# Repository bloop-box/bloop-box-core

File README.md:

# bloop-box-core

[Hardware Documentation](https://bloop-box.github.io/bloop-box-core)

### !!! THIS IS A PROTOTYPE WORK IN PROGRESS !!!

## What does it do?

This board is supposed to replace the Raspberry Pi Zero 2W in the bloop box with a cheaper alternative, using an ESP32-C5.

It will support all functions of the bloop box and can be used as a drop-in-replacement for the Raspi. In addition, due to the capabilities of the ESP32-C5 this will have support for 5GHz WiFi.

## GPIO

| Function       | ESP-Pin |
|:---------------|:--------|
| Button1 (BOOT) | GPIO 28 |
| Button2        | GPIO 27 |
| LED1           | GPIO 25 |
| LED2           | GPIO 26 |
| I2C SCL        | GPIO 3  |
| I2C SDA        | GPIO 2  |
| I2S BCLK       | GPIO 23 |
| I2S DIN        | GPIO 4  |
| I2S LRCLK      | GPIO 24 |
| SPI MISO       | GPIO 9  |
| SPI MOSI       | GPIO 8  |
| SPI SCK        | GPIO 6  |
| NFC CS         | GPIO 10 |
| NFC IRQ        | GPIO 0  |
| NFC RST        | GPIO 1  |
| SD CS          | GPIO 5  |
| SD Detect      | GPIO 7  |
| Serial RX      | GPIO 12 |
| Serial TX      | GPIO 11 |

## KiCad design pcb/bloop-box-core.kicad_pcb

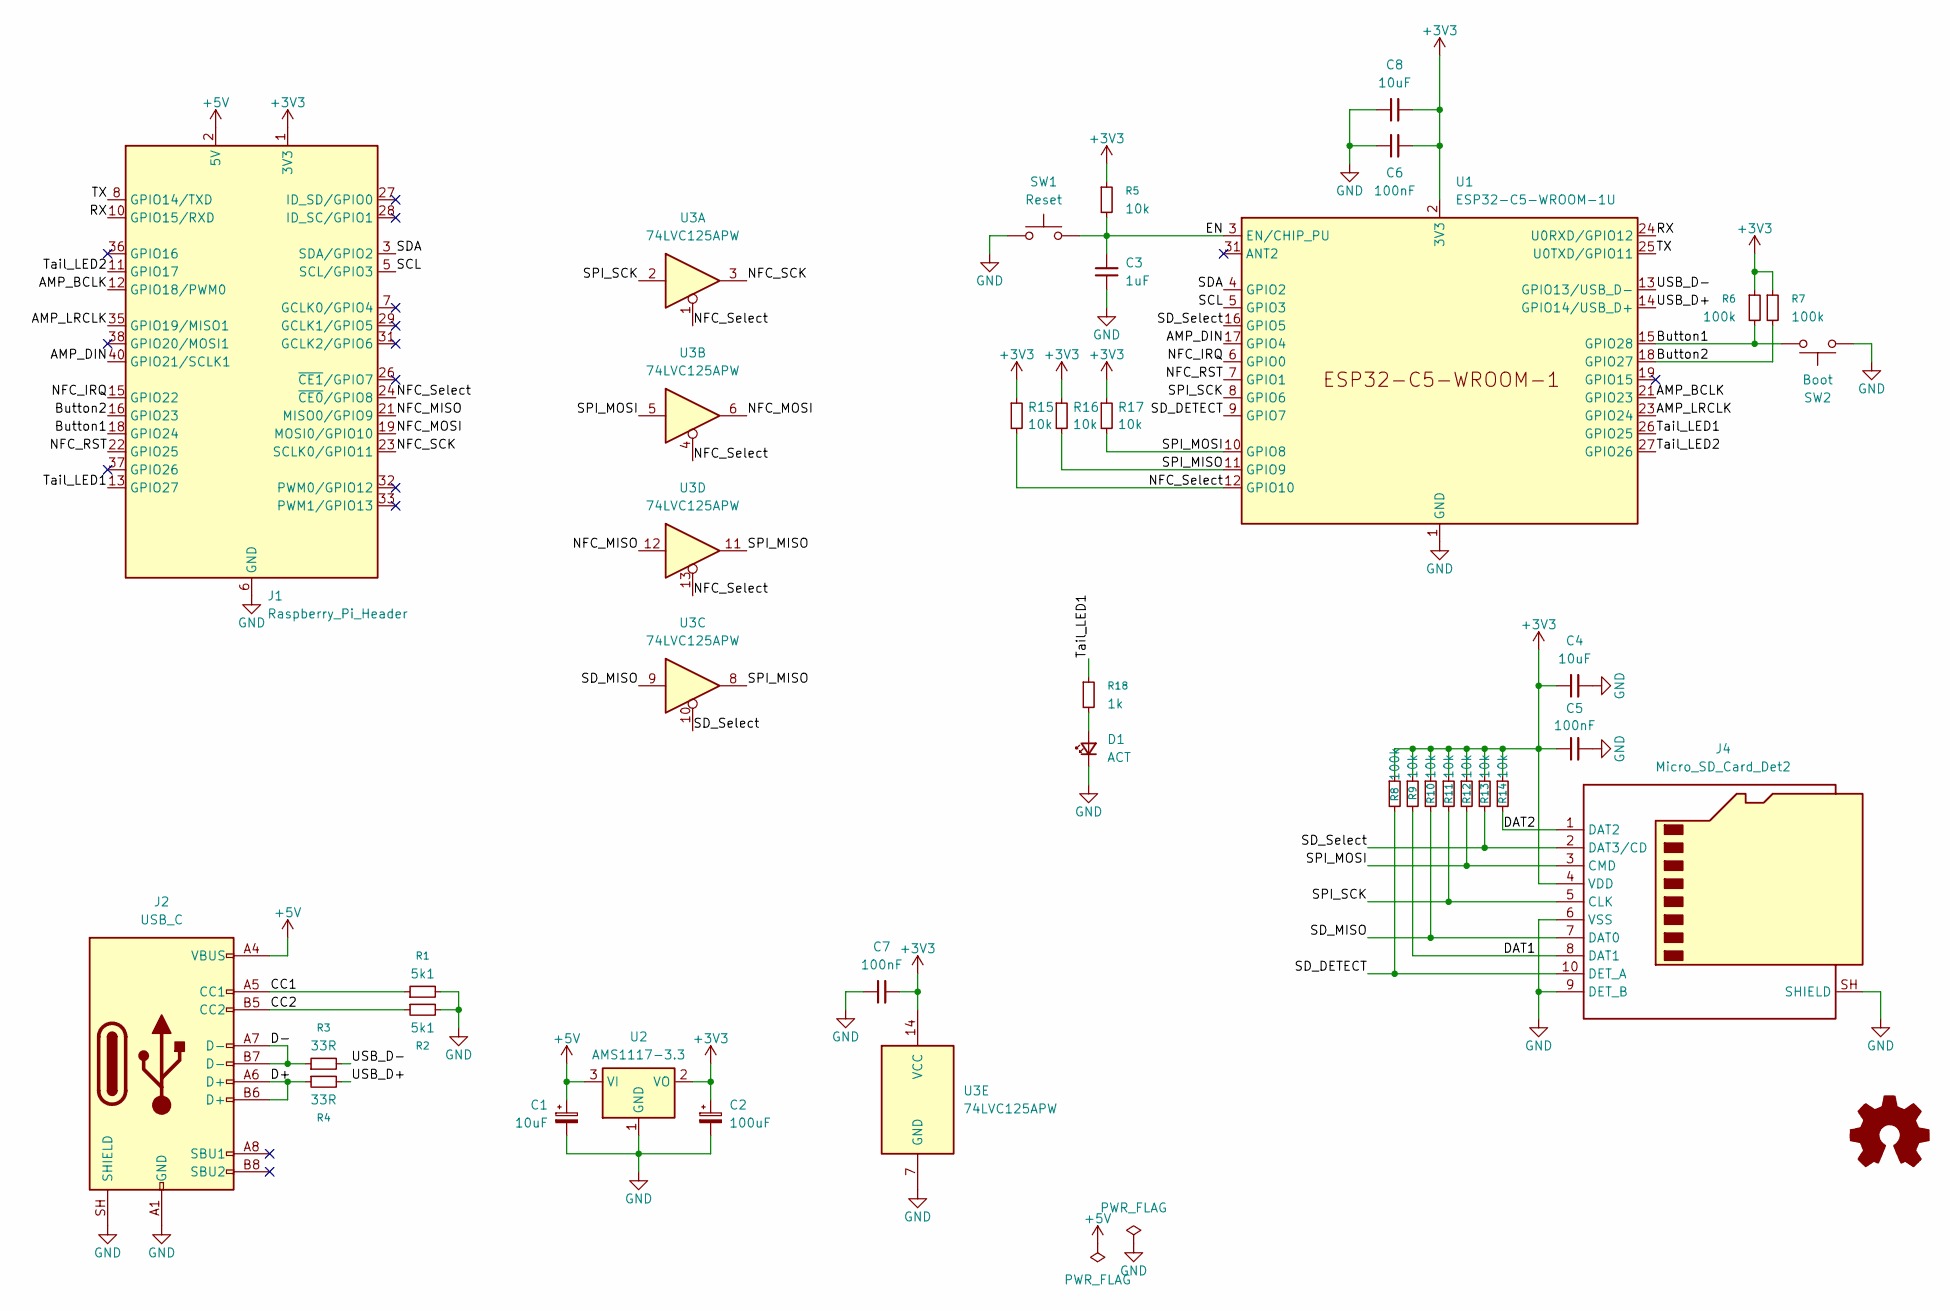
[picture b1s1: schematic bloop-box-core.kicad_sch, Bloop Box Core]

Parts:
C1: 10uF; CP_EIA-3216-18_Kemet-A; LCSC C7171
C2: 100uF; CP_EIA-3528-21_Kemet-B; LCSC C16133
C3: 1uF; C_0402_1005Metric; LCSC C52923
C4, C8: 10uF; C_0402_1005Metric; LCSC C15525
C5, C6, C7: 100nF; C_0402_1005Metric; LCSC C1525
D1: ACT; LED_0603_1608Metric; LCSC C89811
J1: Raspberry_Pi_Header; PinHeader_2x20_P2.54mm_Vertical; LCSC C50980
J2: USB_C; USB_C_Receptacle_GCT_USB4105-xx-A_16P_TopMnt_Horizontal; LCSC C2765186
J4: Micro_SD_Card_Det2; microSD_HC_Molex_104031-0811; LCSC C585350
R1, R2: 5k1; R_0402_1005Metric; LCSC C25905
R3, R4: 33R; R_0402_1005Metric; LCSC C25105
R5, R9, R10, R11, R12, R13, R14, R15, R16, R17: 10k; R_0402_1005Metric; LCSC C25744
R6, R7, R8: 100k; R_0402_1005Metric; LCSC C25741
R18: 1k; R_0402_1005Metric; LCSC C11702
SW1: Reset; SW_Push_SPST_NO_Alps_SKRK; LCSC C720477
SW2: Boot; SW_Push_SPST_NO_Alps_SKRK; LCSC C720477
U1: ESP32-C5-WROOM-1U; LCSC C54951857
U2: AMS1117-3.3; SOT-223-3_TabPin2; LCSC C6186
U3: 74LVC125APW; TSSOP-14_4.4x5mm_P0.65mm; LCSC C6059

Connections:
+3V3: C2.1, C4.2, C5.2, C6.2, C7.2, C8.1, J1.1 (3V3), J1.17 (3V3), J4.4 (VDD), R5.1, R6.1, R7.1, R8.1, R9.1, R10.1, R11.1, R12.1, R13.1, R14.1, R15.1, R16.1, R17.1, U1.2 (3V3), U2.2 (VO), U3.14 (VCC)
+5V: C1.1, J1.2 (5V), J1.4 (5V), J2.A4 (VBUS), J2.A9 (VBUS), J2.B4 (VBUS), J2.B9 (VBUS), U2.3 (VI)
/AMP_BCLK: J1.12 (GPIO18/PWM0), U1.21 (GPIO23)
/AMP_DIN: J1.40 (GPIO21/SCLK1), U1.17 (GPIO4)
/AMP_LRCLK: J1.35 (GPIO19/MISO1), U1.23 (GPIO24)
/Button1: J1.18 (GPIO24), R6.2, SW2.1, U1.15 (GPIO28)
/Button2: J1.16 (GPIO23), R7.2, U1.18 (GPIO27)
/CC1: J2.A5 (CC1), R1.1
/CC2: J2.B5 (CC2), R2.1
/D+: J2.A6 (D+), J2.B6 (D+), R4.1
/D-: J2.A7 (D-), J2.B7 (D-), R3.1
/DAT1: J4.8 (DAT1), R9.2
/DAT2: J4.1 (DAT2), R14.2
/EN: C3.1, R5.2, SW1.2, U1.3 (EN/CHIP_PU)
/NFC_IRQ: J1.15 (GPIO22), U1.6 (GPIO0)
/NFC_MISO: J1.21 (MISO0/GPIO9), U3.12
/NFC_MOSI: J1.19 (MOSI0/GPIO10), U3.6
/NFC_RST: J1.22 (GPIO25), U1.7 (GPIO1)
/NFC_SCK: J1.23 (SCLK0/GPIO11), U3.3
/NFC_Select: J1.24 (~CE0/GPIO8), R15.2, U1.12 (GPIO10), U3.1, U3.4, U3.13
/RX: J1.10 (GPIO15/RXD), U1.24 (U0RXD/GPIO12)
/SCL: J1.5 (SCL/GPIO3), U1.5 (GPIO3)
/SDA: J1.3 (SDA/GPIO2), U1.4 (GPIO2)
/SD_DETECT: J4.10 (DET_A), R8.2, U1.9 (GPIO7)
/SD_MISO: J4.7 (DAT0), R10.2, U3.9
/SD_Select: J4.2 (DAT3/CD), R13.2, U1.16 (GPIO5), U3.10
/SPI_MISO: R16.2, U1.11 (GPIO9), U3.8, U3.11
/SPI_MOSI: J4.3 (CMD), R12.2, R17.2, U1.10 (GPIO8), U3.5
/SPI_SCK: J4.5 (CLK), R11.2, U1.8 (GPIO6), U3.2
/TX: J1.8 (GPIO14/TXD), U1.25 (U0TXD/GPIO11)
/Tail_LED1: J1.13 (GPIO27), R18.1, U1.26 (GPIO25)
/Tail_LED2: J1.11 (GPIO17), U1.27 (GPIO26)
/USB_D+: R4.2, U1.14 (GPIO14/USB_D+)
/USB_D-: R3.2, U1.13 (GPIO13/USB_D-)
GND: C1.2, C2.2, C3.2, C4.1, C5.1, C6.1, C7.1, C8.2, D1.1 (K), J1.6 (GND), J1.9 (GND), J1.14 (GND), J1.20 (GND), J1.25 (GND), J1.30 (GND), J1.34 (GND), J1.39 (GND), J2.A1 (GND), J2.A12 (GND), J2.B1 (GND), J2.B12 (GND), J2.SH (SHIELD), J4.6 (VSS), J4.9 (DET_B), J4.SH (SHIELD), R1.2, R2.2, SW1.1, SW2.2, U1.1 (GND), U1.28 (GND), U1.29 (GND), U1.30 (GND), U1.32 (GND), U2.1 (GND), U3.7 (GND)
unnamed: D1.2 (A), R18.2

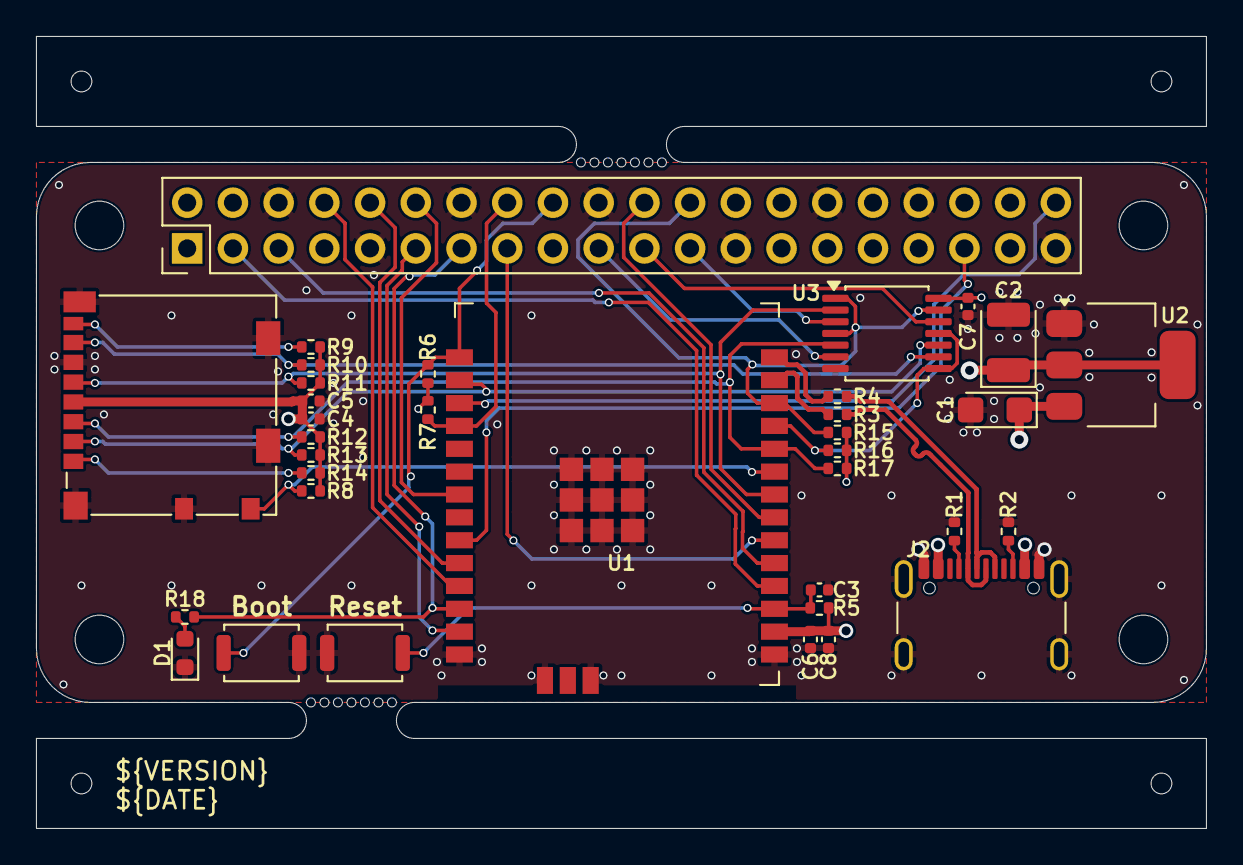
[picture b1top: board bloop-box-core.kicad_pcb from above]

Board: 4 copper layers, 65.0 x 44.0 mm, 37 parts (0 on the bottom side), 36 nets.

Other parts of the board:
mouse-bite-2mm-slot, mouse-bite-2mm-slot#2: VAL**; mouse-bite-2x5mm-slot-onesided-v2
